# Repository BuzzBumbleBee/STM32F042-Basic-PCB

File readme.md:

# Basic STM32F042 breakout baord

This is built around the 20pin STM32F042 package.

features :

* Crystal less USB

Note this is a vary basic desing and lacks a lot things needed
for somthing to use outside of the lab, like ...

* USB ESD protection
* Polarity protection diode
* BOOT0 tied to ground via a 10k or so resistor

The main goal of this project was to get a working STM32 system
with minimal componentss

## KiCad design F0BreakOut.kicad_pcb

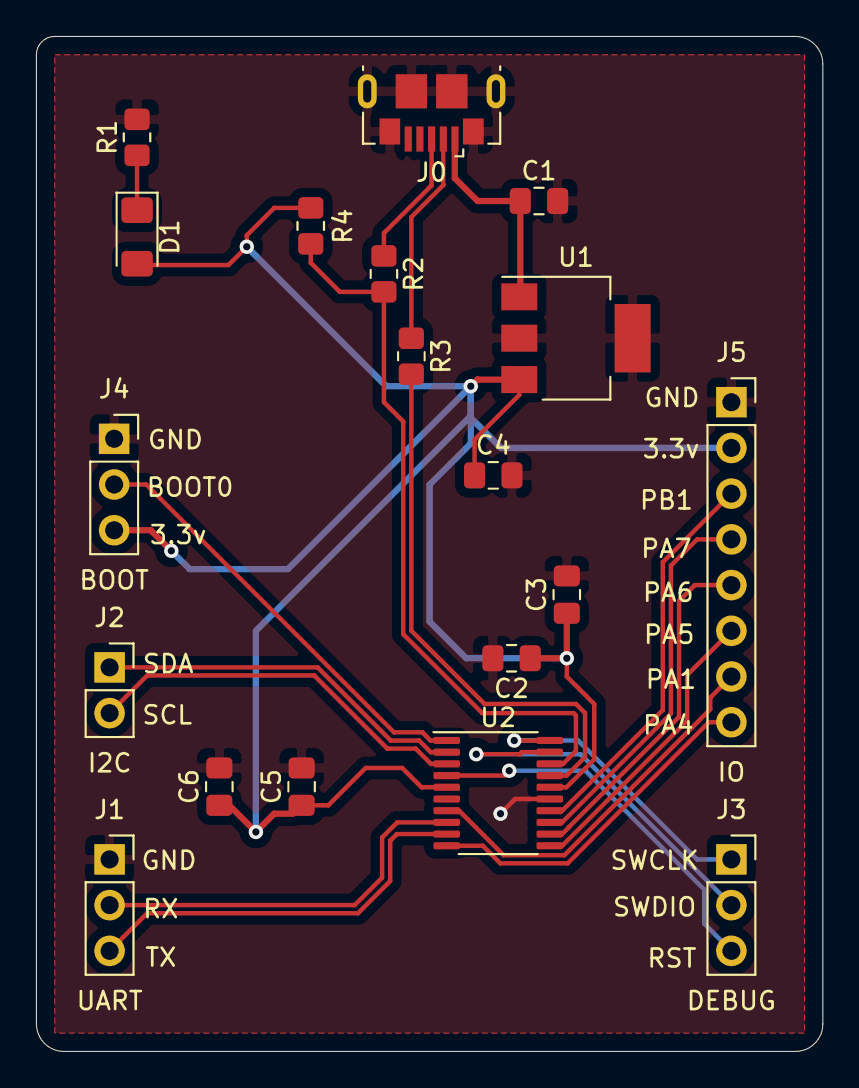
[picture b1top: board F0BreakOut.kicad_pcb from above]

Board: 2 copper layers, 43.7 x 56.4 mm, 19 parts (0 on the bottom side), 22 nets.

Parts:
C1: 22uF; C_0805_2012Metric_Pad1.18x1.45mm_HandSolder
C2, C4, C6: 4.7uF; C_0805_2012Metric_Pad1.18x1.45mm_HandSolder
C3, C5: 100nF; C_0805_2012Metric_Pad1.18x1.45mm_HandSolder
D1: LED_Small; LED_1206_3216Metric_Pad1.42x1.75mm_HandSolder
J0: USB_B_Micro; USB_Micro-B_GCT_USB3076-30-A
J1: UART; PinSocket_1x03_P2.54mm_Vertical
J2: I2C; PinSocket_1x02_P2.54mm_Vertical
J3: DEBUG; PinSocket_1x03_P2.54mm_Vertical
J4: BOOT; PinSocket_1x03_P2.54mm_Vertical
J5: IO; PinSocket_1x08_P2.54mm_Vertical
R1: 1k; R_0805_2012Metric_Pad1.20x1.40mm_HandSolder
R2, R3: 22R; R_0805_2012Metric_Pad1.20x1.40mm_HandSolder
R4: 4.7k; R_0805_2012Metric_Pad1.20x1.40mm_HandSolder
U1: MCP1826S; SOT-223-3_TabPin2
U2: STM32F042F6Px; TSSOP-20_4.4x6.5mm_P0.65mm

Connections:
3.3v: C2.1, C3.1, C4.1, C5.1, C6.1, D1.2, J4.3, J5.2, R4.1, U1.3, U2.5, U2.16
5v: C1.1, J0.1, U1.1
BOOT0: J4.2, U2.1
GND: C1.2, C2.2, C3.2, C4.2, C5.2, C6.2, J0.4, J0.5, J0.6, J1.1, J4.1, J5.1, R1.2, U1.2, U2.15
I2C_SCL: J2.2, U2.3
I2C_SDA: J2.1, U2.2
IO1: J5.3, U2.14
IO2: J5.4, U2.13
IO3: J5.5, U2.12
IO4: J5.6, U2.11
IO5: J5.7, U2.7
IO6: J5.8, U2.10
unnamed: D1.1, R1.1
unnamed: J0.2, R3.1
unnamed: J0.3, R2.1
RST: J3.3, U2.4
SWCLK: J3.1, U2.20
SWDIO: J3.2, U2.19
UART_RX: J1.3, U2.9
UART_TX: J1.2, U2.8
USB_DM: R3.2, U2.17
USB_DP: R2.2, R4.2, U2.18

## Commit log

2021-08-23 Inital Upload
